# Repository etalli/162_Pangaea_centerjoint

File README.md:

# Center joint part for Pangaea keyboard 1.2

This joint part is for Pangaea keyboard by @e3w2q and @otahinosame and @k2. It allows the left and right keyboards to be connected and used as an integrated unit. The angle is 12.5° for each side and 25° for the left and right sides combined.
A switch can also be fitted in the middle of the part. The switch can be attached to the Pangaea function key connector on the wiring and can be used as a Mute/Unmute for remote work, for example.

Also, the distance 0cm version is available.

All the KiCAD design files are avabile, so you can customize the distance or degree as you wish.

## top plate

## switch PCB

## history

* 2023/04/16 rev1.3 completed. distance 1cm version.
* 2023/05/20 added distance 0cm version.

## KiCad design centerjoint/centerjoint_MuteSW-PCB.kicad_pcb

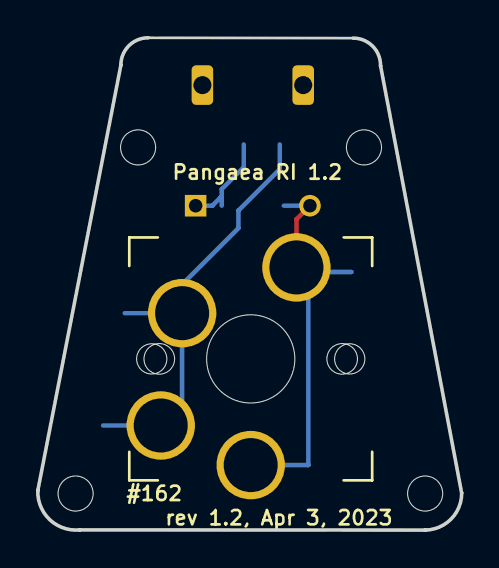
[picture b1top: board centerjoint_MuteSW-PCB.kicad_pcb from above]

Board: 2 copper layers, 23.5 x 27.3 mm, 7 parts (1 on the bottom side), 3 nets.

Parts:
D1: D; diode_TH_SMD_rev3
H1, H2, H3, H4: MountingHole; M2_Hole
J2: Conn_01x04; JST_SH_BM03B-SRSS-TB_1x04-1MP_P1.00mm_Vertical
SW1: SW_Push; CherryMX_Choc_Hotswap_rev9_test

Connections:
SW1: J2.1, SW1.1
SW2: D1.2 (A), SW1.2
TY4: D1.1 (K), J2.3

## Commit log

2023-04-30 updated pcb
2023-05-06 added 0cm version.
2023-05-20 removed unnecessary files.
2023-05-20 removed files.
2023-05-20 moved gitignore file
